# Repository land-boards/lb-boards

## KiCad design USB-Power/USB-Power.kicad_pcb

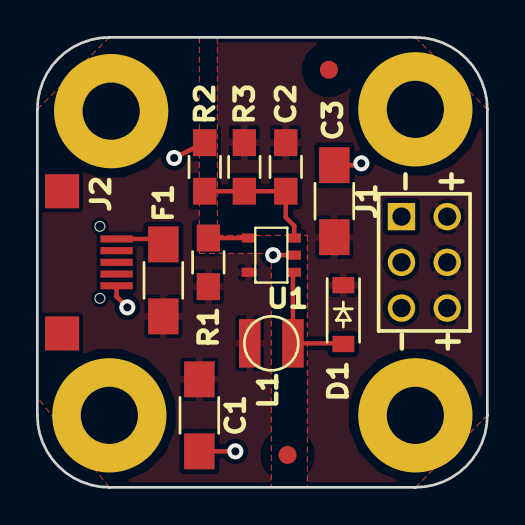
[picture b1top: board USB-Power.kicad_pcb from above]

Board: 2 copper layers, 25.0 x 25.0 mm, 18 parts (0 on the bottom side), 7 nets.

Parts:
C1, C3: 4.7uF; R_1206_HandSoldering
C2: 680pF; R_0805_HandSoldering
D1: MBR0520LT1G; SOD-123-FIXED
F1: FUSE; R_1206_HandSoldering
FID1, FID2: CONN_1; FIDUCIAL
J1: CONN_3X2; PIN_ARRAY_3X2
J2: USB-MICRO-B; USB_Micro-B-Wellco-SMT
L1: 10uH; IND-3MM
MTG1, MTG2, MTG3, MTG4: CONN_1; MTG-4-40
R1: 1M; R_0805_HandSoldering
R2: 1K; R_0805_HandSoldering
R3: 3.09K; R_0805_HandSoldering
U1: LMR62014; SOT23-5

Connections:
/5V Power Supply/+5VOUT: C2.2, C3.1, D1.2, J1.2, J1.4, J1.6, R3.2
/5V Power Supply/VFB: D1.1, L1.2, U1.1
/USB/+5VUSB: C1.1, F1.2, L1.1, R1.1, U1.5
GND: C1.2, C3.2, J1.1, J1.3, J1.5, J2.5, R2.2, U1.2
unnamed: C2.1, R2.1, R3.1, U1.3
unnamed: F1.1, J2.1
unnamed: R1.2, U1.4

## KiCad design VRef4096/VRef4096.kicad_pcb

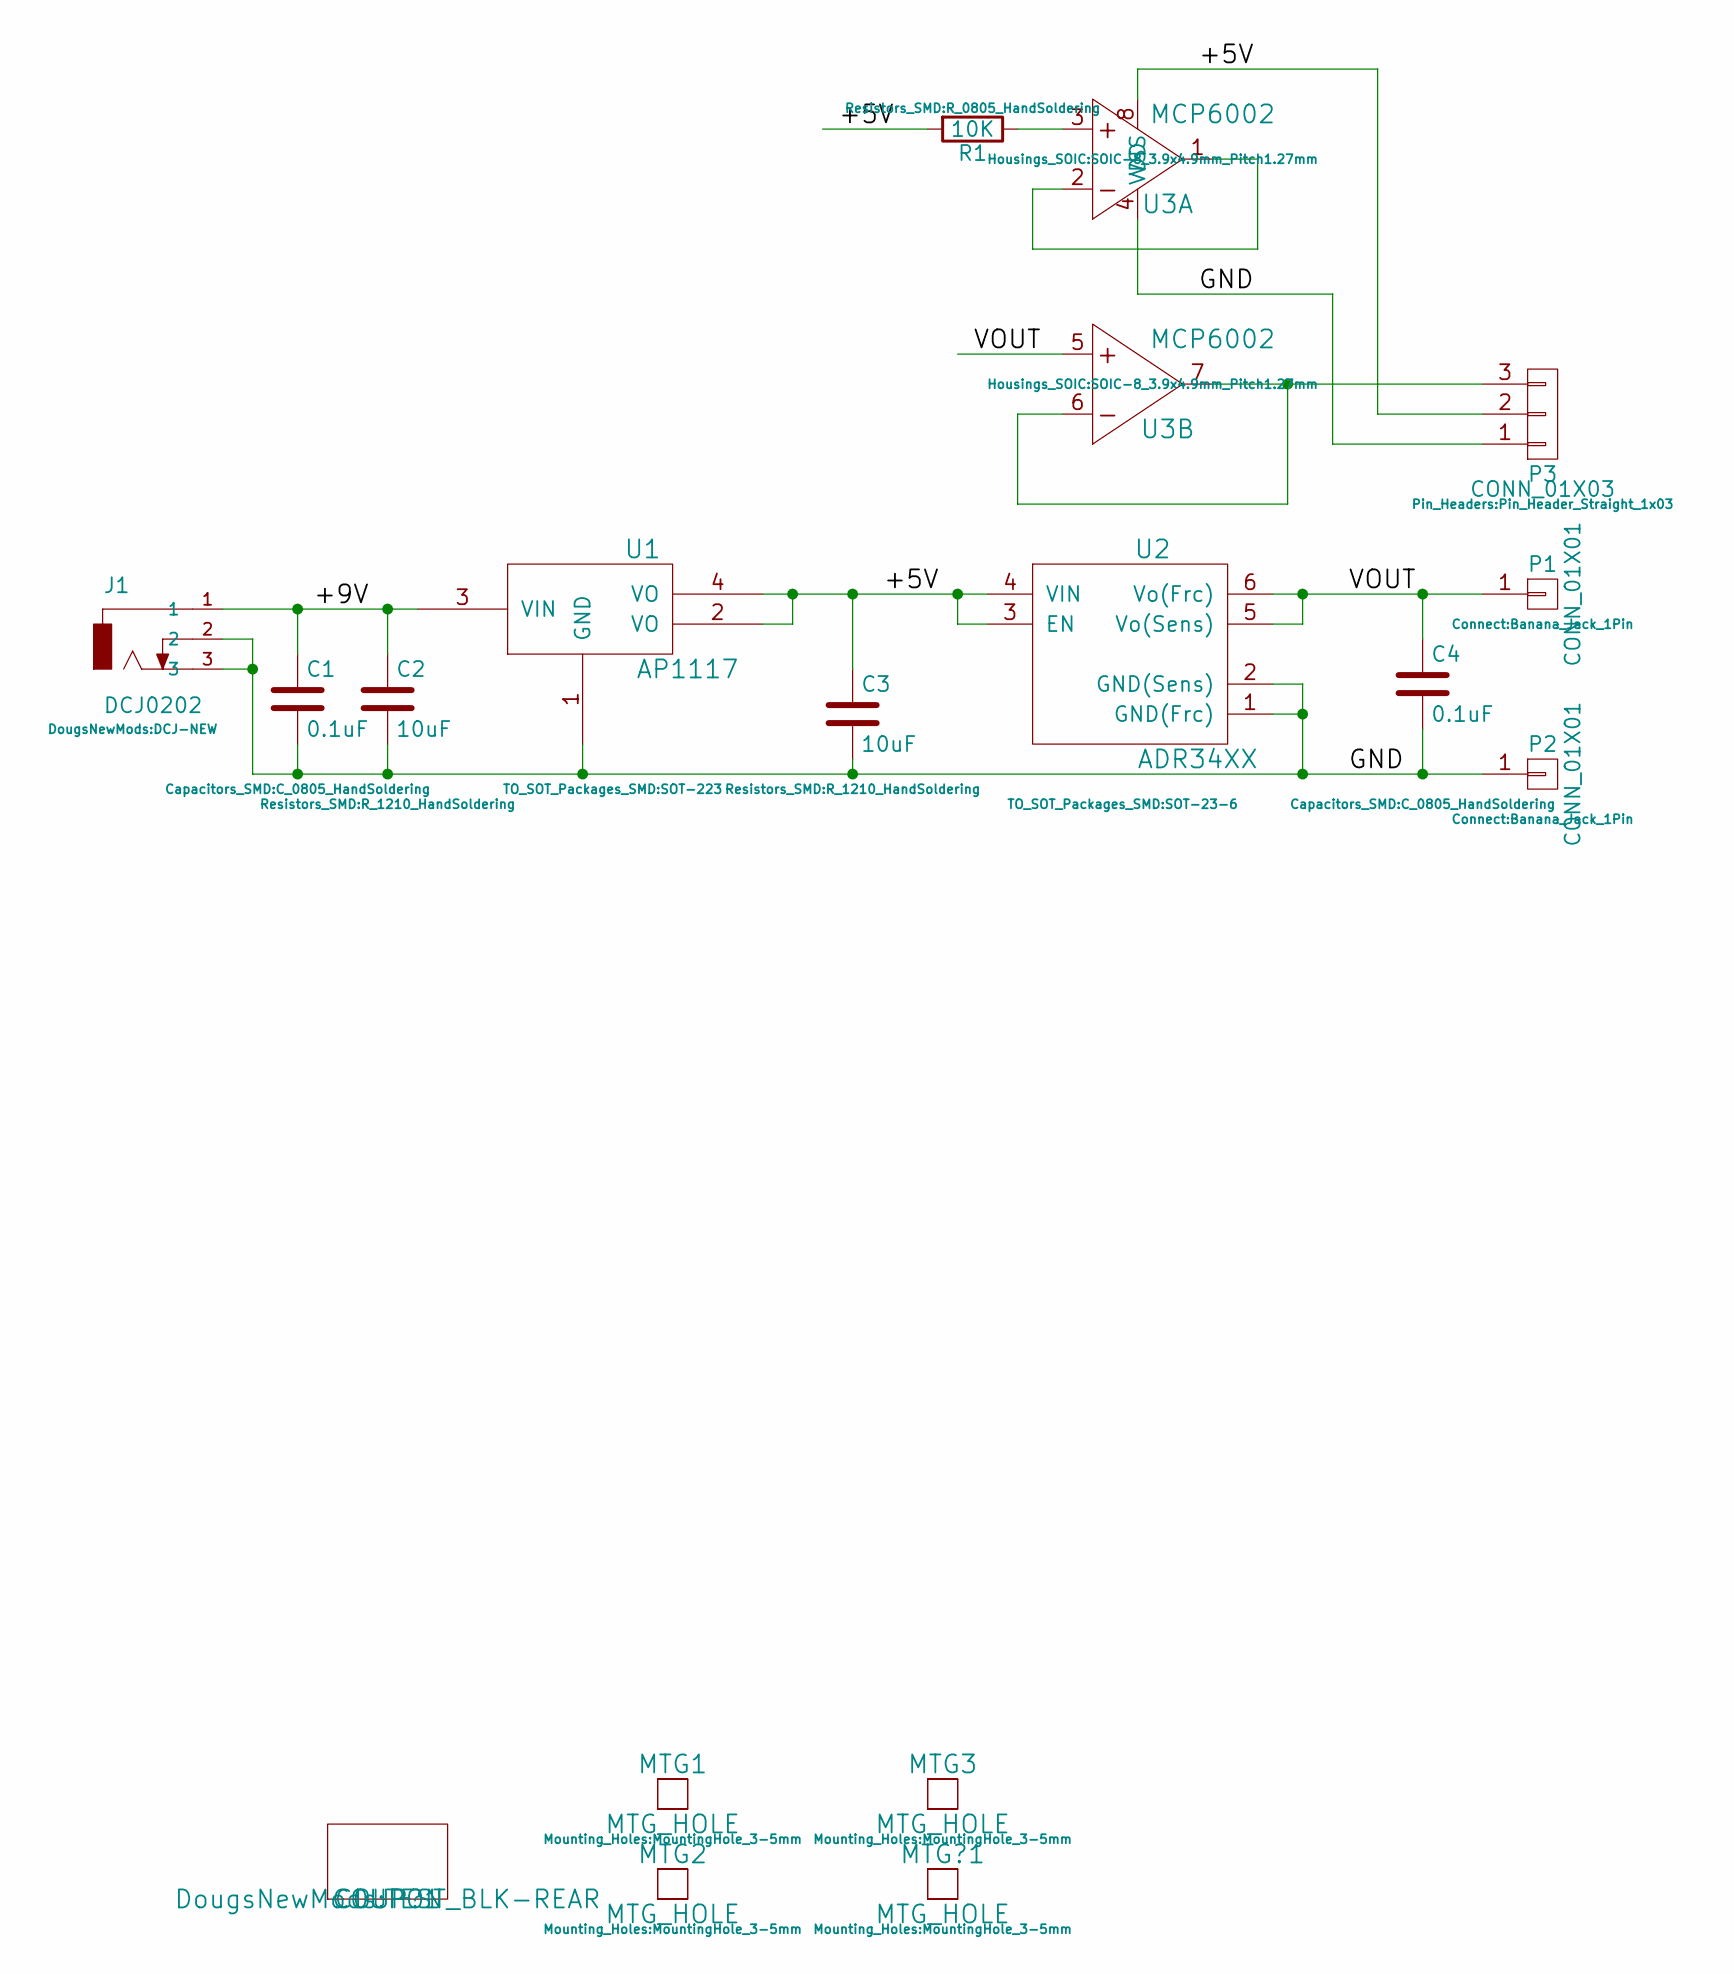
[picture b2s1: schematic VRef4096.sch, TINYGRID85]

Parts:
C1, C4: 0.1uF; C_0805_HandSoldering
C2, C3: 10uF; R_1210_HandSoldering
COUP?1: COUPON; TEST_BLK-REAR
J1: DCJ0202; DCJ-NEW
MTG1, MTG2, MTG3: MTG_HOLE; MountingHole_3-5mm
MTG?1: MTG_HOLE; MountingHole_3-5mm
P1, P2: CONN_01X01; Banana_Jack_1Pin
P3: CONN_01X03; Pin_Header_Straight_1x03
R1: 10K; R_0805_HandSoldering
U1: AP1117; SOT-223
U2: ADR34XX; SOT-23-6
U3: MCP6002; SOIC-8_3.9x4.9mm_Pitch1.27mm

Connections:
/+5V: C3.1, P3.2, R1.2, U1.2 (VO), U1.4 (VO), U2.3 (EN), U2.4 (VIN), U3.8 (VDD)
/+9V: C1.1, C2.1, J1.1, U1.3 (VIN)
/GND: C1.2, C2.2, C3.2, C4.2, J1.2, J1.3, P2.1, P3.1, U1.1 (GND), U2.1 (GND(Frc)), U2.2 (GND(Sens)), U3.4 (VSS)
/VOUT: C4.1, P1.1, U2.5 (Vo(Sens)), U2.6 (Vo(Frc)), U3.5 (+)
unnamed: P3.3, U3.6 (-), U3.7 (Q)
unnamed: R1.1, U3.3 (+)
unnamed: U3.1 (Q), U3.2 (-)

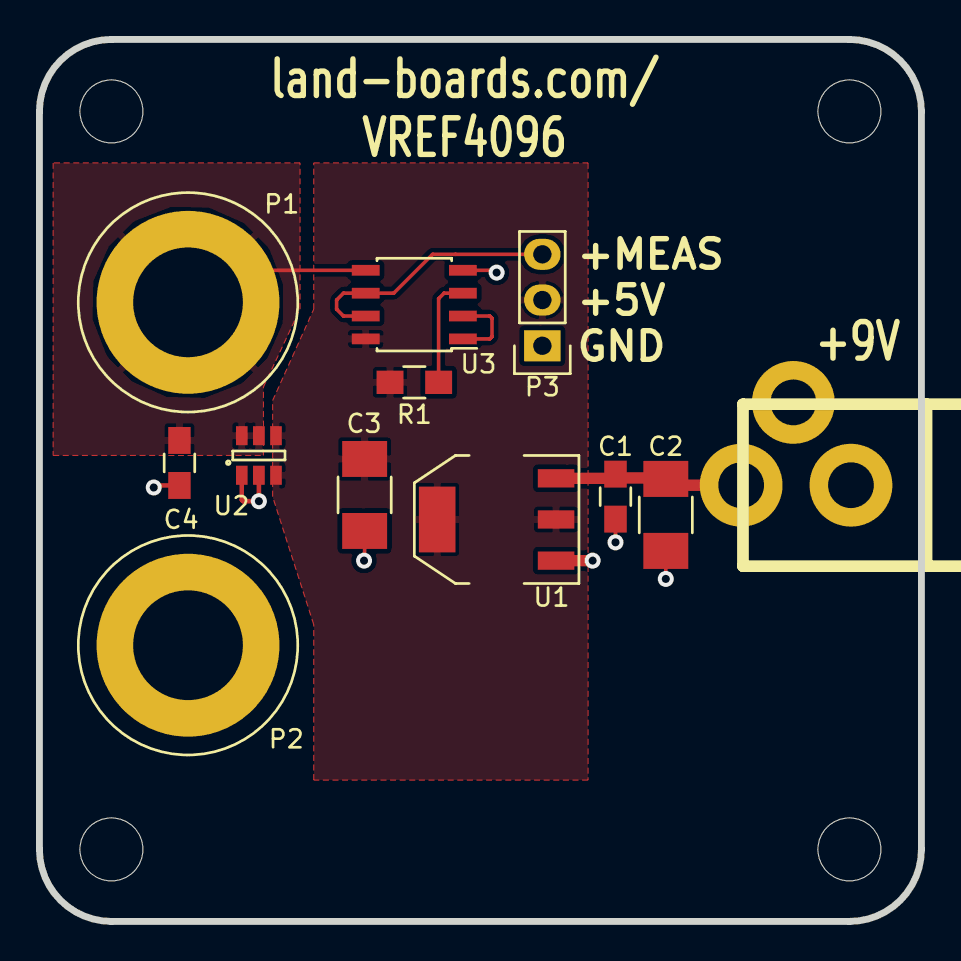
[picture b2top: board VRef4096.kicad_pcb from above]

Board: 2 copper layers, 49.0 x 49.0 mm, 17 parts (0 on the bottom side), 7 nets.

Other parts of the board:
TEST: COUPON; TEST_BLK-REAR

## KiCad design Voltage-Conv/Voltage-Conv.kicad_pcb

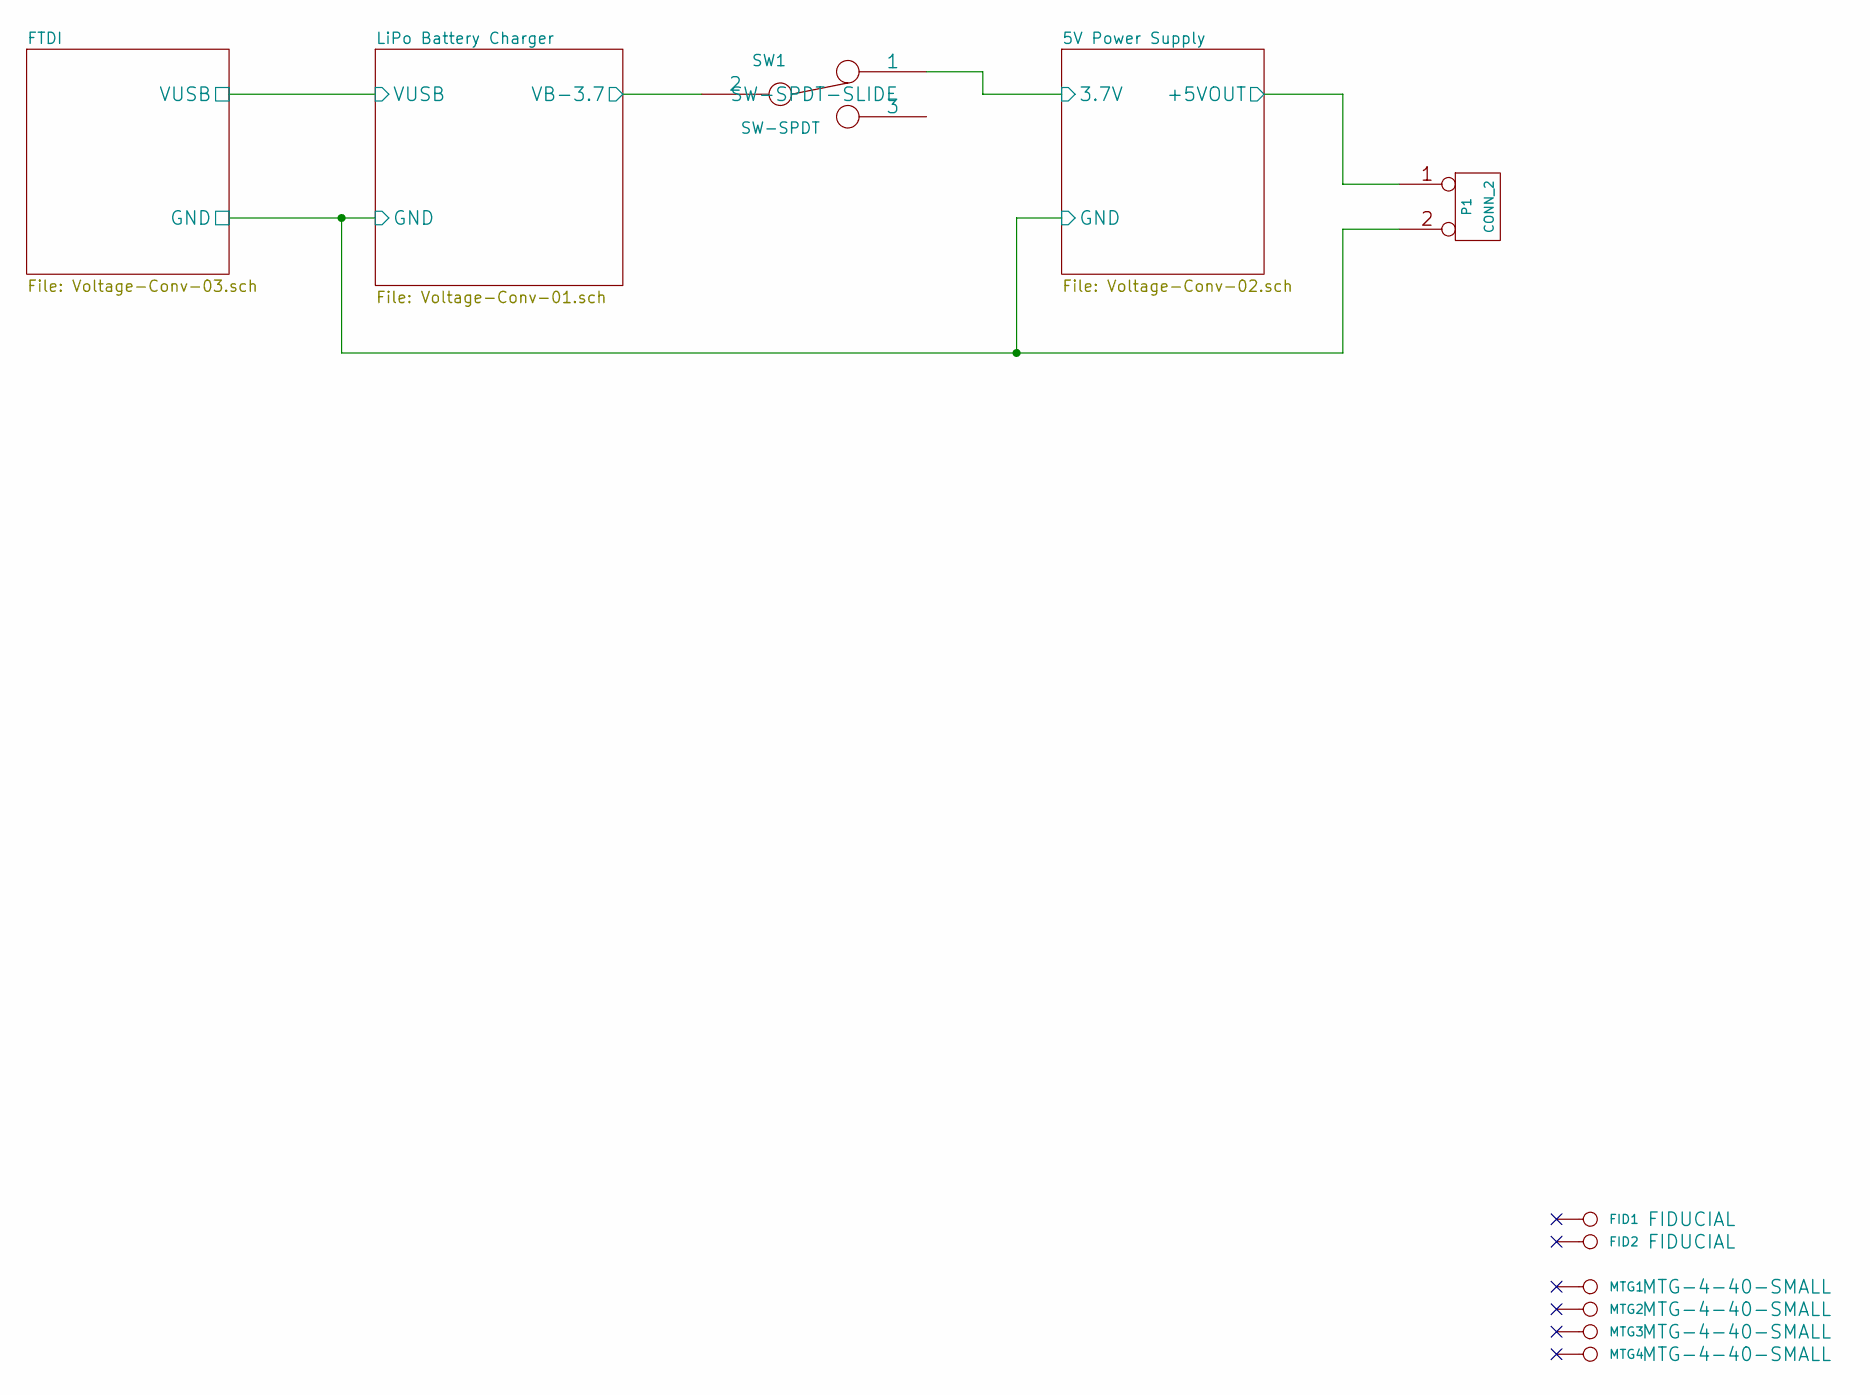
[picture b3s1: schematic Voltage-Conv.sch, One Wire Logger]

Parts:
FID1, FID2: CONN_1; FIDUCIAL
MTG1, MTG2, MTG3, MTG4: CONN_1; MTG-4-40-SMALL
P1: CONN_2
SW1: SW-SPDT; SW-SPDT-SLIDE

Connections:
/5V Power Supply/3.7V: SW1.1; also elsewhere on the board
/5V Power Supply/+5VOUT: P1.1; also elsewhere on the board
/LiPo Battery Charger/VB-3.7: SW1.2; also elsewhere on the board
GND: P1.2 (PM); also elsewhere on the board

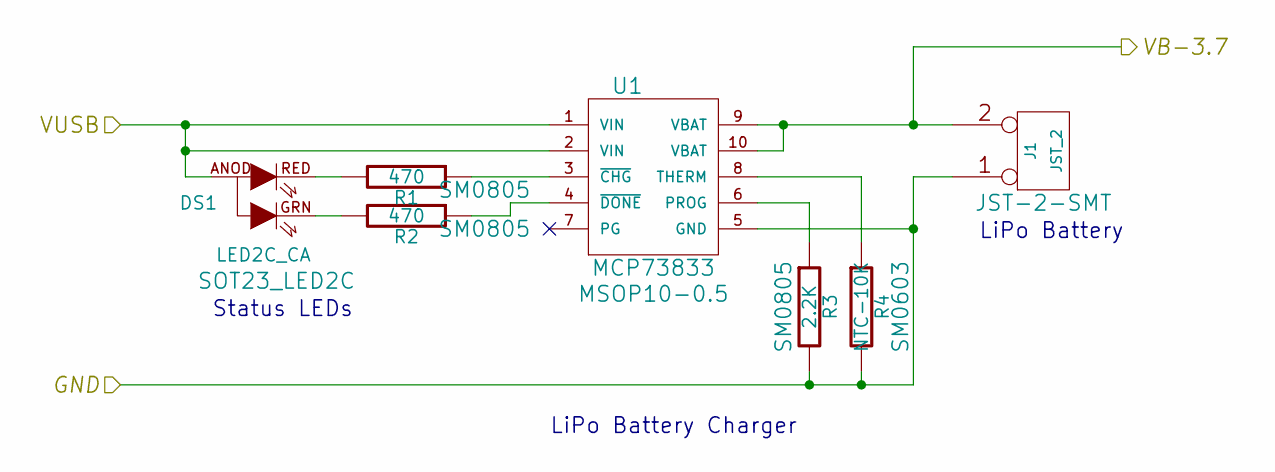
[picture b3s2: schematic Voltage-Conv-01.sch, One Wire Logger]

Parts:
DS1: LED2C_CA; SOT23_LED2C; MfgPN SML-LX15IGC-TR
J1: JST_2; JST-2-SMT; MfgPN S2B-PH-SM4-TB(LF)(SN)
R1, R2: 470; SM0805; MfgPN CR0805-JW-471ELF
R3: 2.2K; SM0805; MfgPN CRCW08052K20JNEB
R4: NTC-10K; SM0603; MfgPN ERT-J1VG103JA
U1: MCP73833; MSOP10-0.5; MfgPN MCP73833-AMI/UN

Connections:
/FTDI/VUSB: DS1.ANOD, U1.1 (VIN), U1.2 (VIN); also elsewhere on the board
/LiPo Battery Charger/VB-3.7: J1.2 (PM), U1.9 (VBAT), U1.10 (VBAT); also elsewhere on the board
GND: J1.1, R3.2, R4.2, U1.5 (GND); also elsewhere on the board
unnamed: R3.1, U1.6 (PROG)
unnamed: R4.1, U1.8 (THERM)
unnamed: DS1.RED, R1.2
unnamed: DS1.GRN, R2.2
unnamed: R1.1, U1.3 (~CHG)
unnamed: R2.1, U1.4 (~DONE)

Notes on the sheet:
LiPo Battery Charger
Status LEDs
LiPo Battery

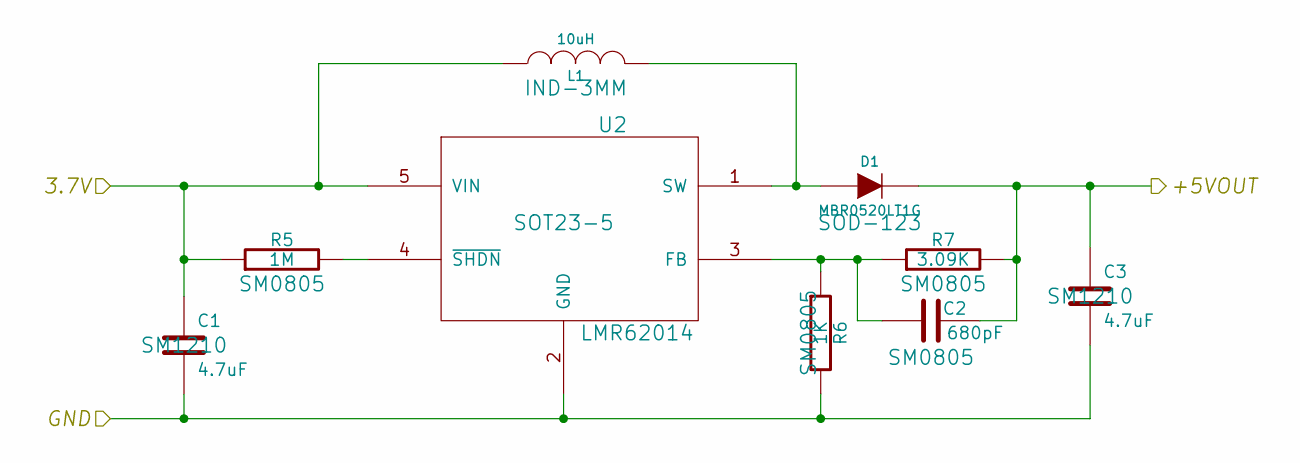
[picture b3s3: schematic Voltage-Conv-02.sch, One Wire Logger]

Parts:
C1, C3: 4.7uF; SM1210; MfgPN VJ1206V475MXJTW1BC
C2: 680pF; SM0805; MfgPN VJ0805Y681JXXCW1BC
D1: MBR0520LT1G; SOD-123; MfgPN MBR0520LT1G
L1: 10uH; IND-3MM; MfgPN SRN3015-100M
R5: 1M; SM0805; MfgPN CRCW08051M00FKEA
R6: 1K; SM0805; MfgPN CRCW08051K00JNEA
R7: 3.09K; SM0805; MfgPN RK73H2ATTE3091F
U2: LMR62014; SOT23-5; MfgPN LMR62014XMFE/NOPB

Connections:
/5V Power Supply/3.7V: C1.1, L1.1, R5.1, U2.5 (VIN); also elsewhere on the board
/5V Power Supply/+5VOUT: C2.2, C3.1, D1.2 (K), R7.2; also elsewhere on the board
GND: C1.2, C3.2, R6.2, U2.2 (GND); also elsewhere on the board
unnamed: C2.1, R6.1, R7.1, U2.3 (FB)
unnamed: R5.2, U2.4 (~SHDN)
unnamed: D1.1 (A), L1.2, U2.1 (SW)

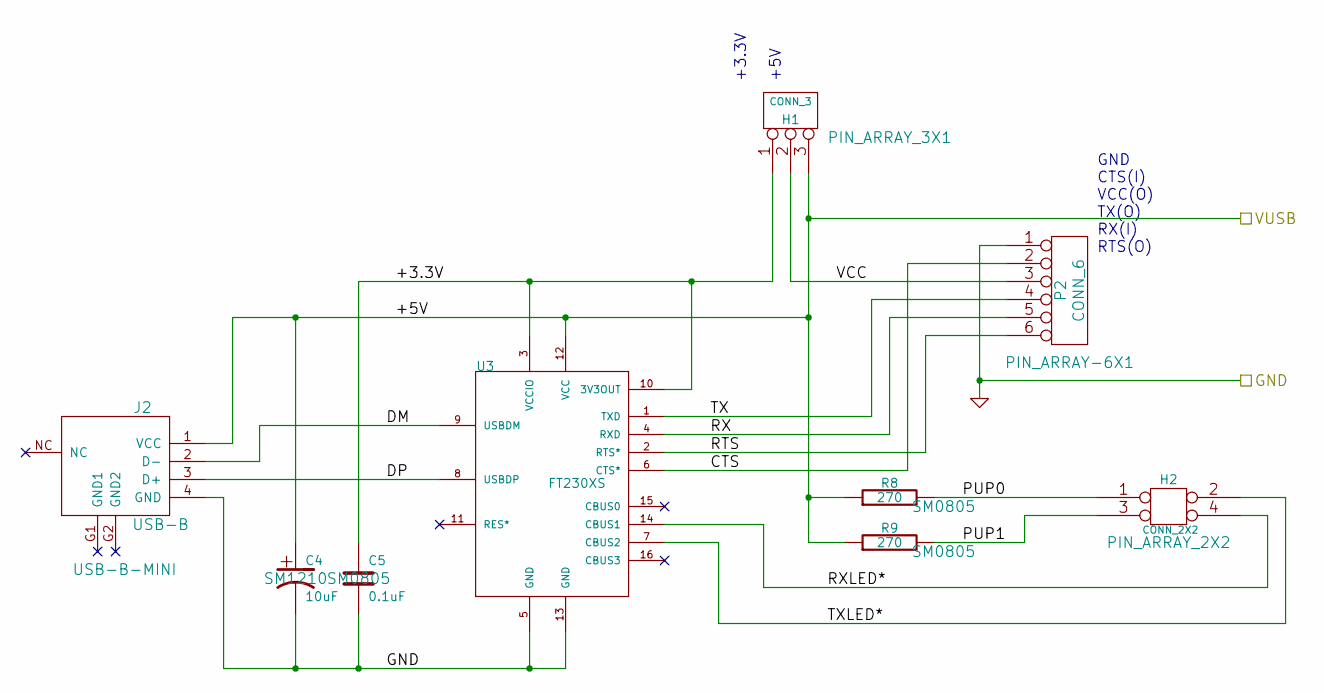
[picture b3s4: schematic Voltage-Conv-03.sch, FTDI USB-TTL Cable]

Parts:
C4: 10uF; SM1210; MfgPN CC121ZKY5V8BB106
C5: 0.1uF; SM0805; MfgPN GRM155F51E104ZA1J
H1: CONN_3; PIN_ARRAY_3X1; MfgPN 68002-103HLF
H2: CONN_2X2; PIN_ARRAY_2X2
J2: USB-B; USB-B-MINI; MfgPN UX60SC-MB-5ST(80)
P2: CONN_6; PIN_ARRAY-6X1; MfgPN 68002-106HLF
R8: 270; SM0805; MfgPN CRG0805F270R
R9: 270; SM0805
U3: FT230XS; ssop-16

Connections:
/FTDI/+3.3V: C5.1, H1.1, U3.3 (VCCIO), U3.10 (3V3OUT)
/FTDI/CTS: P2.2, U3.6 (CTS*)
/FTDI/DM: J2.2 (D-), U3.9 (USBDM)
/FTDI/DP: J2.3 (D+), U3.8 (USBDP)
/FTDI/PUP0: H2.1, R8.2
/FTDI/PUP1: H2.3, R9.2
/FTDI/RTS: P2.6, U3.2 (RTS*)
/FTDI/RX: P2.5, U3.4 (RXD)
/FTDI/RXLED*: H2.4, U3.14 (CBUS1)
/FTDI/TX: P2.4, U3.1 (TXD)
/FTDI/TXLED*: H2.2, U3.7 (CBUS2)
/FTDI/VCC: H1.2 (PM), P2.3
/FTDI/VUSB: C4.1, H1.3, J2.1 (VCC), R8.1, R9.1, U3.12 (VCC); also elsewhere on the board
GND: C4.2, C5.2, J2.4 (GND), P2.1, U3.5 (GND), U3.13 (GND); also elsewhere on the board

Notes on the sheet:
GND CTS(I) VCC(O) TX(O) RX(I) RTS(O)
+3.3V +5V

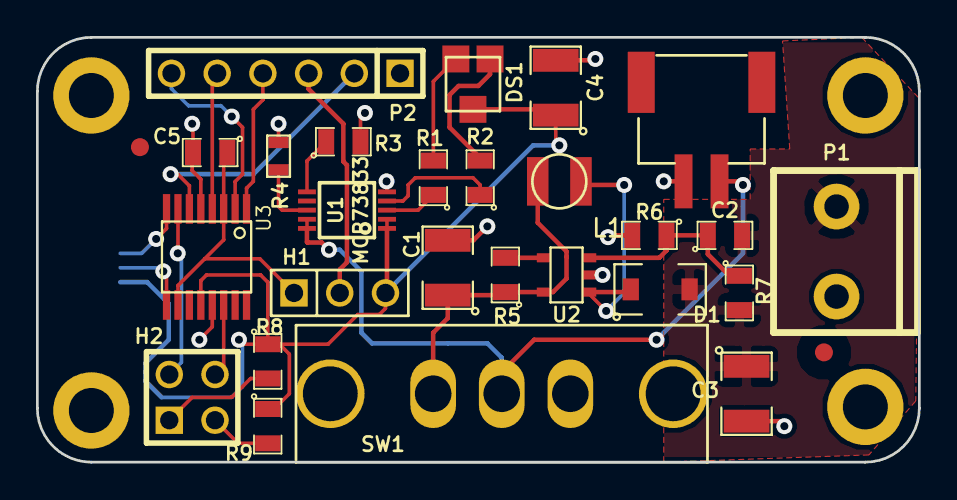
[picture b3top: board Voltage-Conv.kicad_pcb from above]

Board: 2 copper layers, 49.0 x 23.6 mm, 33 parts (1 on the bottom side), 26 nets.

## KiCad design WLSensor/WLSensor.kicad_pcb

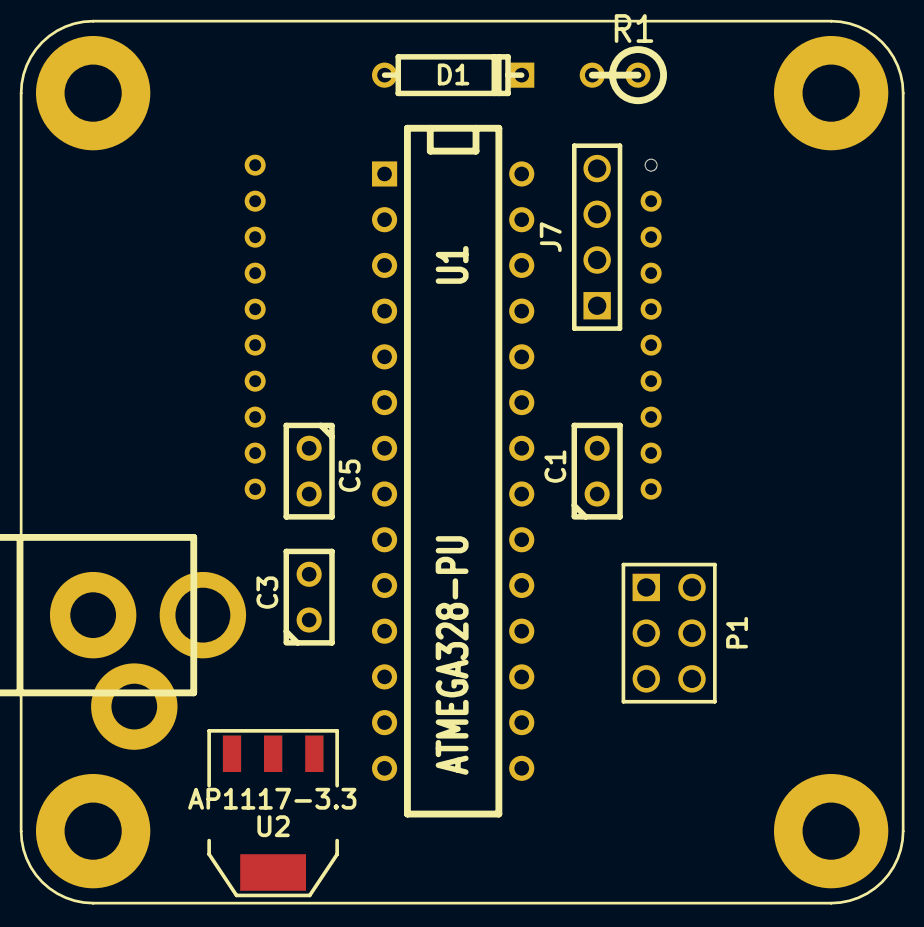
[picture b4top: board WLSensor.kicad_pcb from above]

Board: 2 copper layers, 12 parts (1 on the bottom side), 11 nets, no tracks yet.

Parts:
BD1: 49x49mm Board; BD-49X49
C1, C3, C5: 0.1uF; C1
D1: 4N4004; D3
J2: DCJ0202; JACK_3.5MM
J7: CONN_4; PIN_ARRAY_4x1
M1: XBEE; xbee_r1-XBEE
P1: CONN_3X2; pin_array_3x2
R1: 10K; R1
U1: ATMEGA328-PU; DIP-28__300
U2: AP1117-3.3; SOT223

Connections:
+5V: C5.1, D1.2, J7.2, P1.2, R1.1, U1.7, U1.20, U2.2, U2.4
/MicroProcessor/AD4: J7.3, U1.27
/MicroProcessor/AD5: J7.4, U1.28
/MicroProcessor/ARDRES: D1.1, P1.5, R1.2, U1.1
/MicroProcessor/AREF: C1.1, U1.21
/MicroProcessor/D1: U1.3, U1.4
/MicroProcessor/MISO: P1.1, U1.18
/MicroProcessor/MOSI: P1.4, U1.17
/MicroProcessor/SCK: P1.3, U1.19
/MicroProcessor/VIN: C3.1, J2.1, U2.3
GND: C1.2, C3.2, C5.2, J2.2, J2.3, J7.1, P1.6, U1.8, U1.22, U2.1

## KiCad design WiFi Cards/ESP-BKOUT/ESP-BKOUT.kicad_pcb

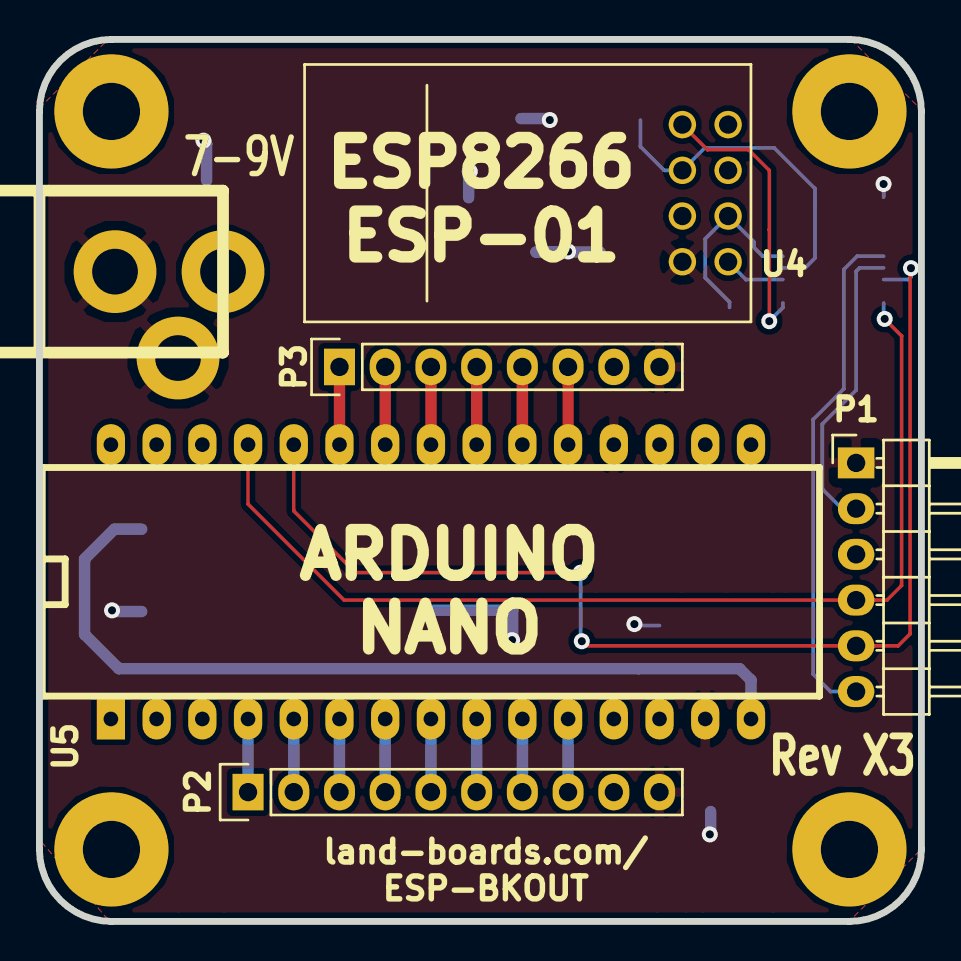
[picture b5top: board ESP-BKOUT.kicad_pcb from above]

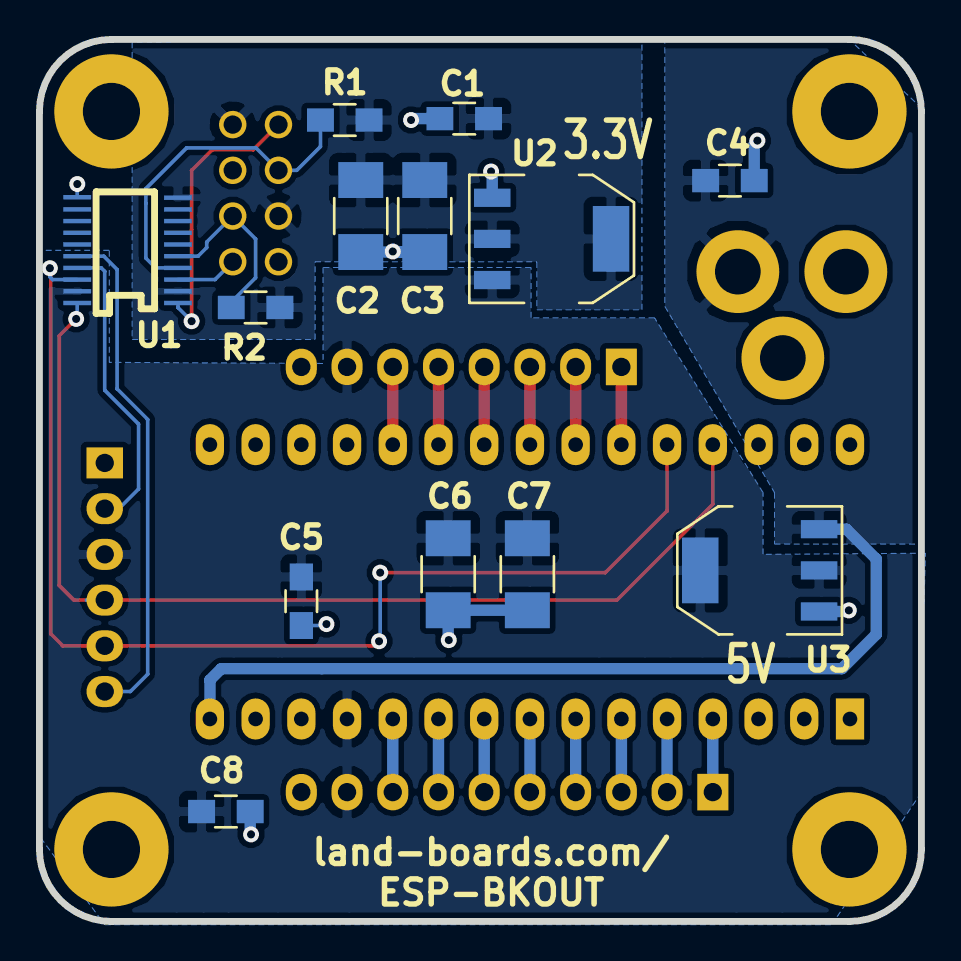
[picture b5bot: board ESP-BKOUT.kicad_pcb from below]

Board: 2 copper layers, 49.0 x 49.0 mm, 23 parts (13 on the bottom side), 26 nets.

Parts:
C1, C4, C5, C8: 0.1uF; R_0805_HandSoldering
C2, C3, C6, C7: 22uF; R_1210_HandSoldering
J1: DCJ0202; DCJ-NEW
MTG1, MTG2, MTG3, MTG4: CONN_1; MTG-4-40
P1: FTDI; Pin_Header_Angled_1x06
P2: CONN_01X10; Pin_Header_Straight_1x10
P3: CONN_01X08; Pin_Header_Straight_1x08
R1: 1K; R_0805_HandSoldering
R2: 3.3K; R_0805_HandSoldering
U1: TXS0108; SOG20
U2: AP1117-3.3V; SOT-223
U3: AZ1117-5.0V; SOT-223
U4: ESP8266-ESP-01
U5: arduino_nano; arduino_mini

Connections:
+3V3: C1.1, C2.1, C3.1, R1.2, R2.2, U1.2, U1.10, U2.2, U2.4, U4.4, U4.7
+5V: C5.1, C6.1, C7.1, C8.1, P1.3, P2.9, P3.7, U1.19, U2.3, U3.2, U3.4, U5.12
+9V: C4.1, J1.1, U3.3, U5.15
/A0: P2.1, U5.4
/A1: P2.2, U5.5
/A2: P2.3, U5.6
/A3: P2.4, U5.7
/A6: P2.7, U5.10
/A7: P2.8, U5.11
/ARDRXD: P1.5, U1.18, U5.26
/ARDTXD: P1.4, U1.20, U5.27
/D2: P3.6, U5.20
/D3: P3.5, U5.21
/D4: P3.4, U5.22
/D5: P3.3, U5.23
/D6: P3.2, U5.24
/D7: P3.1, U5.25
/DTR: P1.2, U1.17
/ESPDTR: R1.1, U1.4, U4.6
/ESPRTS: R2.1, U1.5, U4.3
/ESPRXD: U1.1, U4.8
/ESPTXD: U1.3, U4.1
/RTS: P1.6, U1.16
/SCL: P2.6, U5.9
/SDA: P2.5, U5.8
GND: C1.2, C2.2, C3.2, C4.2, C5.2, C6.2, C7.2, C8.2, J1.2, J1.3, P1.1, P2.10, P3.8, U1.11, U2.1, U3.1, U4.2, U5.14, U5.19

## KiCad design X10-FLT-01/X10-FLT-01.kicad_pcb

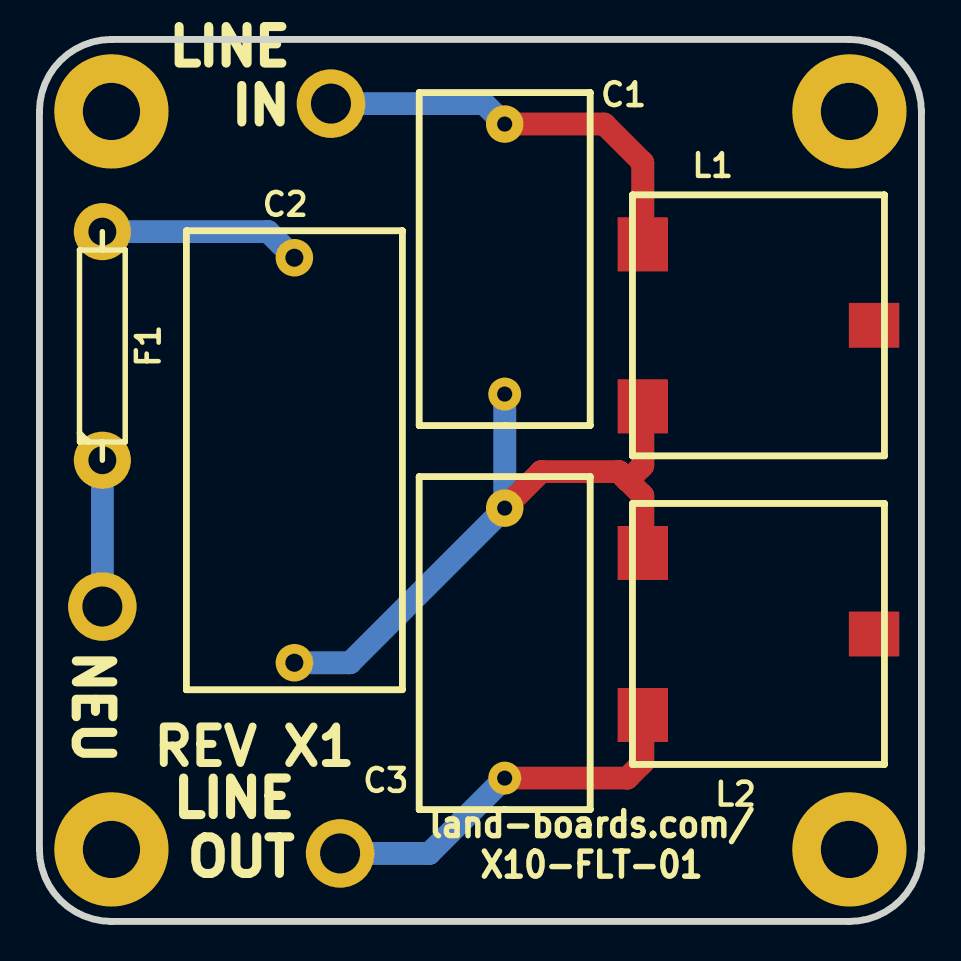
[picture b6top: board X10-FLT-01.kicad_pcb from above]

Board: 2 copper layers, 49.0 x 49.0 mm, 13 parts (0 on the bottom side), 5 nets.

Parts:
C1, C3: 0.22uF; C15MM
C2: 1uF; C25MM
F1: FUSE; FUSE-18AWG
L1, L2: 8uH; L15MM
MTG1, MTG2, MTG3, MTG4: MTG_HOLE; MTG-4-40
P1, P2, P3: CONN_1; HOLE-12AWG

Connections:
unnamed: C2.2, F1.2
unnamed: F1.1, P2.1
unnamed: C3.2, L2.1, P3.1
unnamed: C1.2, C2.1, C3.1, L1.1, L2.2
unnamed: C1.1, L1.2, P1.1
